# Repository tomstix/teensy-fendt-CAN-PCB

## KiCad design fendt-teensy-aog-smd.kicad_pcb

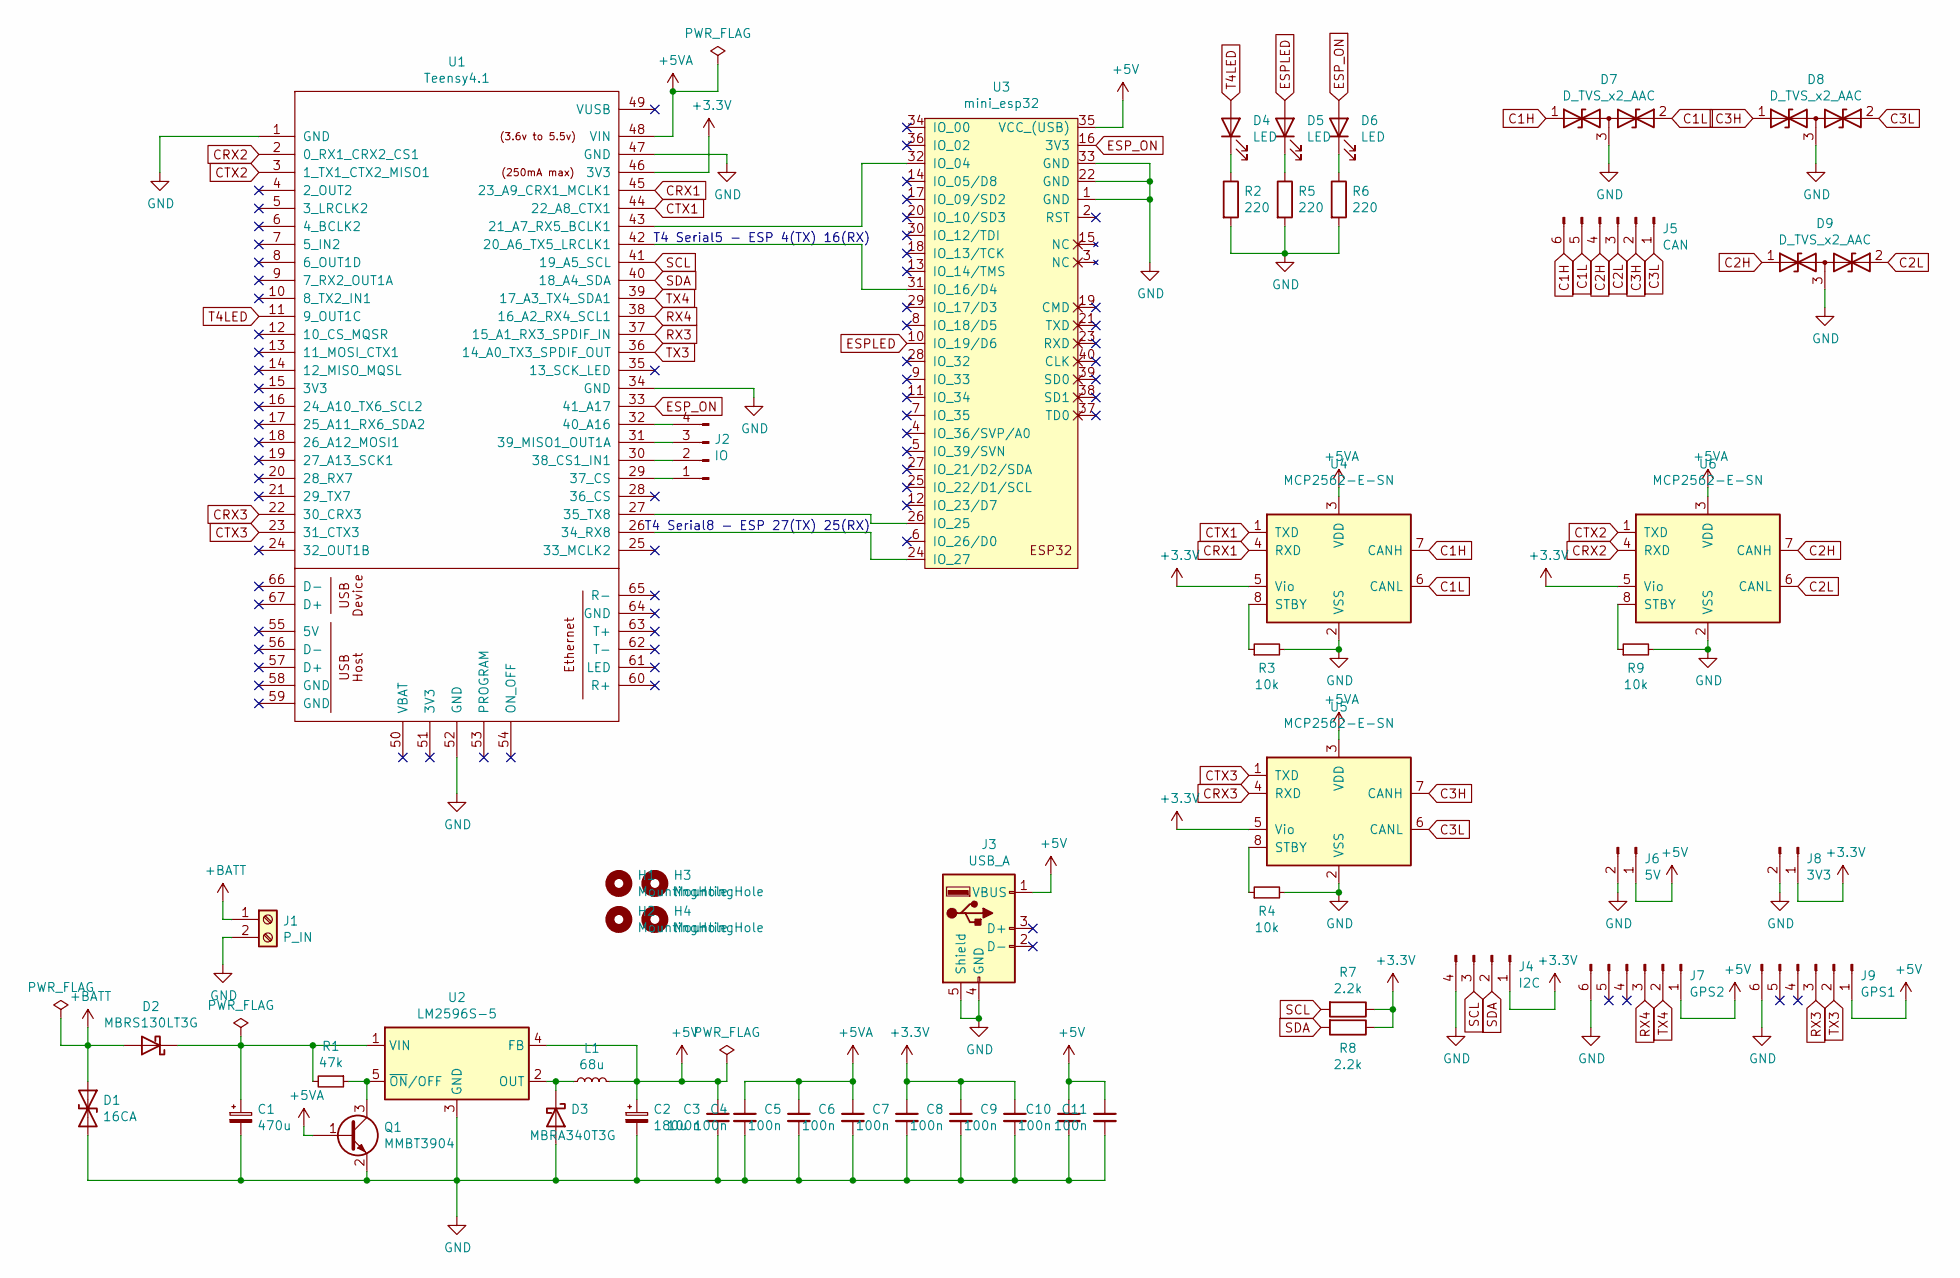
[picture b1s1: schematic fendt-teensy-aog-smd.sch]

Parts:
C1: 470u; CP_Radial_D8.0mm_P5.00mm
C2: 180u; CP_Radial_D8.0mm_P3.50mm
C3, C4, C5, C6, C7, C8, C9, C10, C11: 100n; C_0805_2012Metric_Pad1.18x1.45mm_HandSolder
D1: 16CA; D_SMB_Handsoldering
D2: MBRS130LT3G; D_SMB_Handsoldering
D3: MBRA340T3G; D_SMA_Handsoldering
D4, D5, D6: LED; LED_1206_3216Metric_Pad1.42x1.75mm_HandSolder
D7, D8, D9: D_TVS_x2_AAC; SOT-23
H1, H2, H3, H4: MountingHole; MountingHole_3.2mm_M3_DIN965
J1: P_IN; TerminalBlock_RND_205-00276_1x02_P5.00mm_Vertical
J2: IO; JST_XH_B4B-XH-A_1x04_P2.50mm_Vertical
J3: USB_A; USB_A_CONNFLY_DS1095-WNR0
J4: I2C; JST_XH_B4B-XH-A_1x04_P2.50mm_Vertical
J5: CAN; Wago_734-166_1x06_P3.50mm_Horizontal
J6: 5V; JST_XH_B2B-XH-A_1x02_P2.50mm_Vertical
J7: GPS2; JST_XH_B6B-XH-A_1x06_P2.50mm_Vertical
J8: 3V3; JST_XH_B2B-XH-A_1x02_P2.50mm_Vertical
J9: GPS1; JST_XH_B6B-XH-A_1x06_P2.50mm_Vertical
L1: 68u; L_Fastron_PISR_Handsoldering
Q1: MMBT3904; SOT-23
R1: 47k; R_Axial_DIN0207_L6.3mm_D2.5mm_P7.62mm_Horizontal
R2, R5, R6: 220; R_Axial_DIN0207_L6.3mm_D2.5mm_P7.62mm_Horizontal
R3, R4, R9: 10k; R_Axial_DIN0207_L6.3mm_D2.5mm_P7.62mm_Horizontal
R7, R8: 2.2k; R_Axial_DIN0207_L6.3mm_D2.5mm_P7.62mm_Horizontal
U1: Teensy4.1; Teensy41
U2: LM2596S-5; TO-263-5_TabPin3
U3: mini_esp32; ESP32_mini
U4, U5, U6: MCP2562-E-SN; SOIC-8_3.9x4.9mm_P1.27mm

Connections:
+3V3: C7.1, C8.1, C9.1, J4.1, J8.1, R7.1, R8.1, U1.46 (3V3), U4.5 (Vio), U5.5 (Vio), U6.5 (Vio)
+5V: C2.1, C3.1, C10.1, C11.1, J3.1 (VBUS), J6.1, J7.1, J9.1, L1.2, U2.4 (FB), U3.35 (VCC_(USB))
+5VA: C4.1, C5.1, C6.1, Q1.1 (B), U1.48 (VIN), U4.3 (VDD), U5.3 (VDD), U6.3 (VDD)
+BATT: D1.1 (A1), D2.2 (A), J1.1
C1H: D7.1 (A1), J5.6, U4.7 (CANH)
C1L: D7.2 (A2), J5.5, U4.6 (CANL)
C2H: D9.1 (A1), J5.4, U6.7 (CANH)
C2L: D9.2 (A2), J5.3, U6.6 (CANL)
C3H: D8.1 (A1), J5.2, U5.7 (CANH)
C3L: D8.2 (A2), J5.1, U5.6 (CANL)
CRX1: U1.45 (23_A9_CRX1_MCLK1), U4.4 (RXD)
CRX2: U1.2 (0_RX1_CRX2_CS1), U6.4 (RXD)
CRX3: U1.22 (30_CRX3), U5.4 (RXD)
CTX1: U1.44 (22_A8_CTX1), U4.1 (TXD)
CTX2: U1.3 (1_TX1_CTX2_MISO1), U6.1 (TXD)
CTX3: U1.23 (31_CTX3), U5.1 (TXD)
ESPLED: D5.2 (A), U3.10 (IO_19/D6)
ESP_ON: D6.2 (A), U1.33 (41_A17), U3.16 (3V3)
GND: C1.2, C2.2, C3.2, C4.2, C5.2, C6.2, C7.2, C8.2, C9.2, C10.2, C11.2, D1.2 (A2), D3.2 (A), D7.3 (common), D8.3 (common), D9.3 (common), J1.2, J3.4 (GND), J3.5 (Shield), J4.4, J6.2, J7.6, J8.2, J9.6, Q1.2 (E), R2.2, R3.2, R4.2, R5.2, R6.2, R9.2, U1.1 (GND), U1.34 (GND), U1.47 (GND), U1.52 (GND), U2.3 (GND), U3.1 (GND), U3.22 (GND), U3.33 (GND), U4.2 (VSS), U5.2 (VSS), U6.2 (VSS)
unnamed: C1.1, D2.1 (K), R1.2, U2.1 (VIN)
unnamed: D3.1 (K), L1.1, U2.2 (OUT)
unnamed: D4.1 (K), R2.1
unnamed: D5.1 (K), R5.1
unnamed: D6.1 (K), R6.1
unnamed: J2.1, U1.29 (37_CS)
unnamed: J2.2, U1.30 (38_CS1_IN1)
unnamed: J2.3, U1.31 (39_MISO1_OUT1A)
unnamed: J2.4, U1.32 (40_A16)
unnamed: Q1.3 (C), R1.1, U2.5 (~ON~/OFF)
unnamed: R3.1, U4.8 (STBY)
unnamed: R4.1, U5.8 (STBY)
unnamed: R9.1, U6.8 (STBY)
unnamed: U1.26 (34_RX8), U3.24 (IO_27)
unnamed: U1.27 (35_TX8), U3.26 (IO_25)
unnamed: U1.42 (20_A6_TX5_LRCLK1), U3.31 (IO_16/D4)
unnamed: U1.43 (21_A7_RX5_BCLK1), U3.32 (IO_04)
RX3: J9.3, U1.37 (15_A1_RX3_SPDIF_IN)
RX4: J7.3, U1.38 (16_A2_RX4_SCL1)
SCL: J4.3, R7.2, U1.41 (19_A5_SCL)
SDA: J4.2, R8.2, U1.40 (18_A4_SDA)
T4LED: D4.2 (A), U1.11 (9_OUT1C)
TX3: J9.2, U1.36 (14_A0_TX3_SPDIF_OUT)
TX4: J7.2, U1.39 (17_A3_TX4_SDA1)

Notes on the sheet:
T4 Serial5 - ESP 4(TX) 16(RX)
T4 Serial8 - ESP 27(TX) 25(RX)

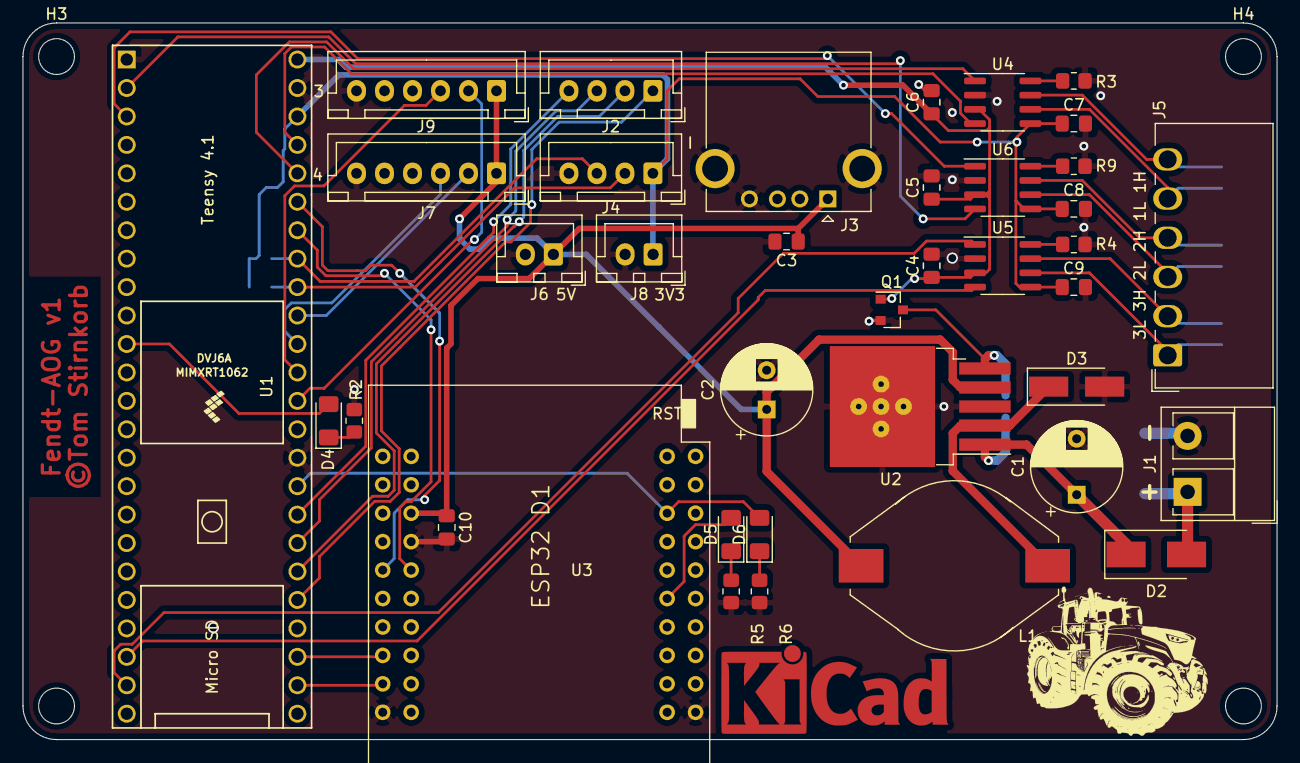
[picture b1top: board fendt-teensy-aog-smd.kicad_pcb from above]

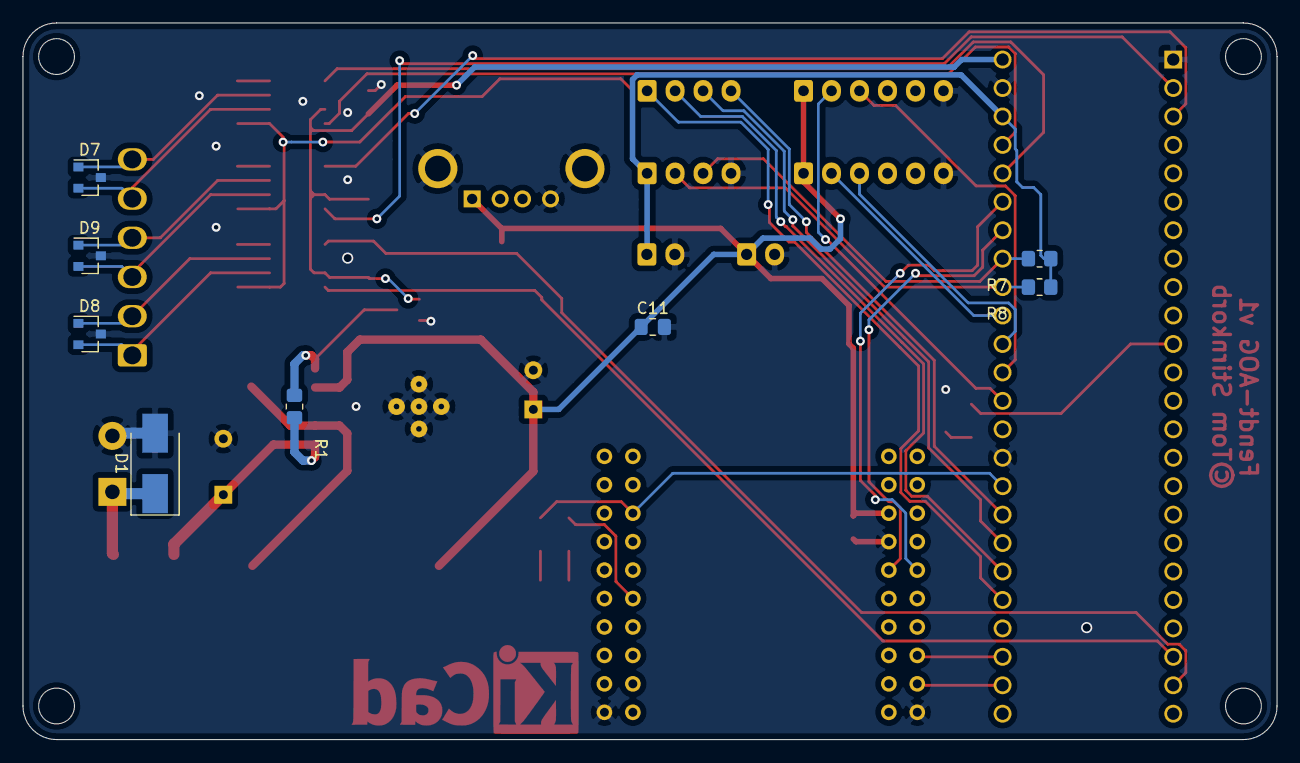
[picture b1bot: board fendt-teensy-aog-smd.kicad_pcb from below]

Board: 2 copper layers, 112.0 x 64.0 mm, 50 parts (8 on the bottom side), 43 nets.

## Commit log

2021-04-20 init
2021-04-20 add schematic

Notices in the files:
fendt-teensy-aog-smd.kicad_pcb:
©Tom Stirnkorb
